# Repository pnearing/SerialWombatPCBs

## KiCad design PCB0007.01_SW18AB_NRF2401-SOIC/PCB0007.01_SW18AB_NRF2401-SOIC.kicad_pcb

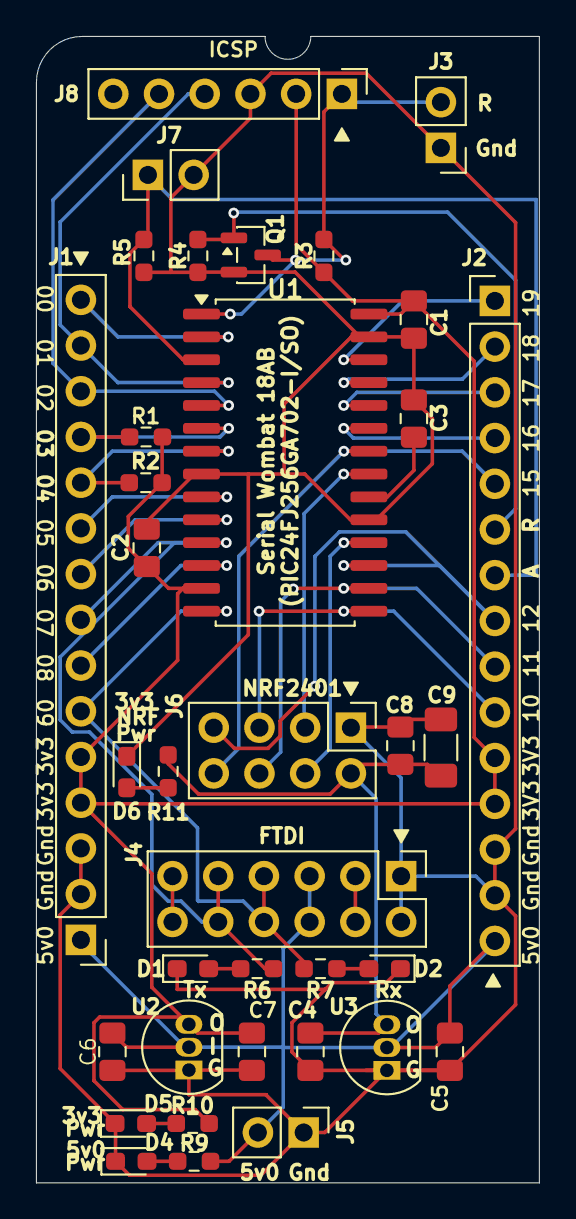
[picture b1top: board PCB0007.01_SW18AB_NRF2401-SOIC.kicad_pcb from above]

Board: 2 copper layers, 27.9 x 63.7 mm, 36 parts (0 on the bottom side), 35 nets.

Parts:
C1, C2, C8: 100nF (0805); C_0805_2012Metric_Pad1.18x1.45mm_HandSolder
C3: 10μF (0805); C_0805_2012Metric_Pad1.18x1.45mm_HandSolder
C4, C5, C6, C7: 1μF (0805); C_0805_2012Metric_Pad1.18x1.45mm_HandSolder
C9: 22µF (1206); C_1206_3216Metric_Pad1.33x1.80mm_HandSolder
D1: Green; D_0603_1608Metric_Pad1.05x0.95mm_HandSolder
D2: Yellow; D_0603_1608Metric_Pad1.05x0.95mm_HandSolder
D4, D5, D6: Red; D_0603_1608Metric_Pad1.05x0.95mm_HandSolder
J1, J2: Male - 1x15; PinHeader_1x15_P2.54mm_Vertical
J3, J7: Male - 1x2; PinHeader_1x02_P2.54mm_Vertical
J4: Male - 2x6; PinHeader_2x06_P2.54mm_Vertical
J5: Male +5v In Header; PinHeader_1x02_P2.54mm_Vertical
J6: Female - 2x4; PinHeader_2x04_P2.54mm_Vertical
J8: Male - 1x6; PinHeader_1x06_P2.54mm_Vertical
Q1: MMBT3904; SOT-23
R1: 2.2KΩ; R_0603_1608Metric_Pad0.98x0.95mm_HandSolder
R2: 2.2KΩ (0603); R_0603_1608Metric_Pad0.98x0.95mm_HandSolder
R3: 10KΩ (0603); R_0603_1608Metric_Pad0.98x0.95mm_HandSolder
R4: 100 KΩ (0603); R_0603_1608Metric_Pad0.98x0.95mm_HandSolder
R5: ?Ω (0603); R_0603_1608Metric_Pad0.98x0.95mm_HandSolder
R6, R7, R9, R10, R11: 330Ω (0605); R_0603_1608Metric_Pad0.98x0.95mm_HandSolder
U1: SerialWombat 18AB - SOIC 28; SOIC-28W_7.5x17.9mm_P1.27mm
U2, U3: MCP1700x-330xxTO; TO-92_Inline

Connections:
+3V3: C1.1, C2.1, C7.1, J1.11, J1.12, J2.11, J2.12, J8.2, R1.1, R2.1, R3.1, R10.1, U1.13 (VDD_+3v3), U1.28 (VDD_+3v3), U2.3 (VO)
+5V: C5.1, C6.1, J1.15, J2.15, J4.5, J4.6, J5.2, R9.1, U2.2 (VI), U3.2 (VI)
/+3V3_NRF: C4.1, C8.1, C9.1, J6.2, R11.1, U3.3 (VO)
/Addr: J2.7, J7.1, R5.1, U1.3 (Addr)
/CTS: J4.3, J4.4
/GPIO_Reset_Input: J2.6, Q1.1 (B), R4.1
/MCLR_(Reset): J3.2, J8.1, Q1.3 (C), R3.2, U1.1 (MCLR_(Reset))
/RTS: J4.11, J4.12
/S.W.P00: J1.1, U1.2 (S.W.P00)
/S.W.P01: J1.2, J8.4, U1.4 (S.W.P01)
/S.W.P02: J1.3, J8.5, U1.5 (S.W.P02)
/S.W.P03(SDA): J1.4, R1.2, U1.6 (S.W.P03(SDA))
/S.W.P04(SCL): J1.5, R2.2, U1.7 (S.W.P04(SCL))
/S.W.P05: J1.6, U1.9 (S.W.P05)
/S.W.P06: J1.7, U1.10 (S.W.P06)
/S.W.P07(TX): J1.8, J4.9, J4.10, R6.1, U1.11 (S.W.P07(TX))
/S.W.P08: J1.9, U1.12 (S.W.P08)
/S.W.P09(RX): J1.10, J4.7, J4.8, R7.1, U1.14 (S.W.P09(RX,5v))
/S.W.P10(SCK): J2.10, J6.5, U1.15 (SW.P10(5v))
/S.W.P11(MOSI): J2.9, J6.6, U1.16 (S.W.P11(5v))
/S.W.P12(MISO): J2.8, J6.7, U1.17 (S.W.P12(5v))
/S.W.P13(CS): J6.4, U1.18 (S.W.P13)
/S.W.P14(CE): J6.3, U1.21 (S.W.P14(5v))
/S.W.P15(IRQ): J2.5, J6.8, U1.22 (S.W.P15(5v))
/S.W.P16: J2.4, U1.23 (S.W.P16)
/S.W.P17: J2.3, U1.24 (S.W.P17)
/S.W.P18: J2.2, U1.25 (S.W.P18)
/S.W.P19: J2.1, U1.26 (S.W.P19)
/VCAP: C3.1, U1.20 (VCAP)
GND: C1.2, C2.2, C3.2, C4.2, C5.2, C6.2, C7.2, C8.2, C9.2, D1.1 (K), D2.1 (K), D4.1 (K), D5.1 (K), D6.1 (K), J1.13, J1.14, J2.13, J2.14, J3.1, J4.1, J4.2, J5.1, J6.1, J7.2, J8.3, Q1.2 (E), R4.2, R5.2, U1.8 (GND), U1.19 (GND), U1.27 (GND), U2.1 (GND), U3.1 (GND)
unnamed: D1.2 (A), R6.2
unnamed: D2.2 (A), R7.2
unnamed: D4.2 (A), R9.2
unnamed: D5.2 (A), R10.2
unnamed: D6.2 (A), R11.2

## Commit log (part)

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2025-06-26 Adding BUZZ Board V2 for OSHW certification
2025-06-26 Adding PCB0031 V2 for OSHW certification
2025-06-29 Adding SW8B Backpack V3 Hardware
2025-07-02 Uploading SW8B Bridge V3 for OSHWA certification
